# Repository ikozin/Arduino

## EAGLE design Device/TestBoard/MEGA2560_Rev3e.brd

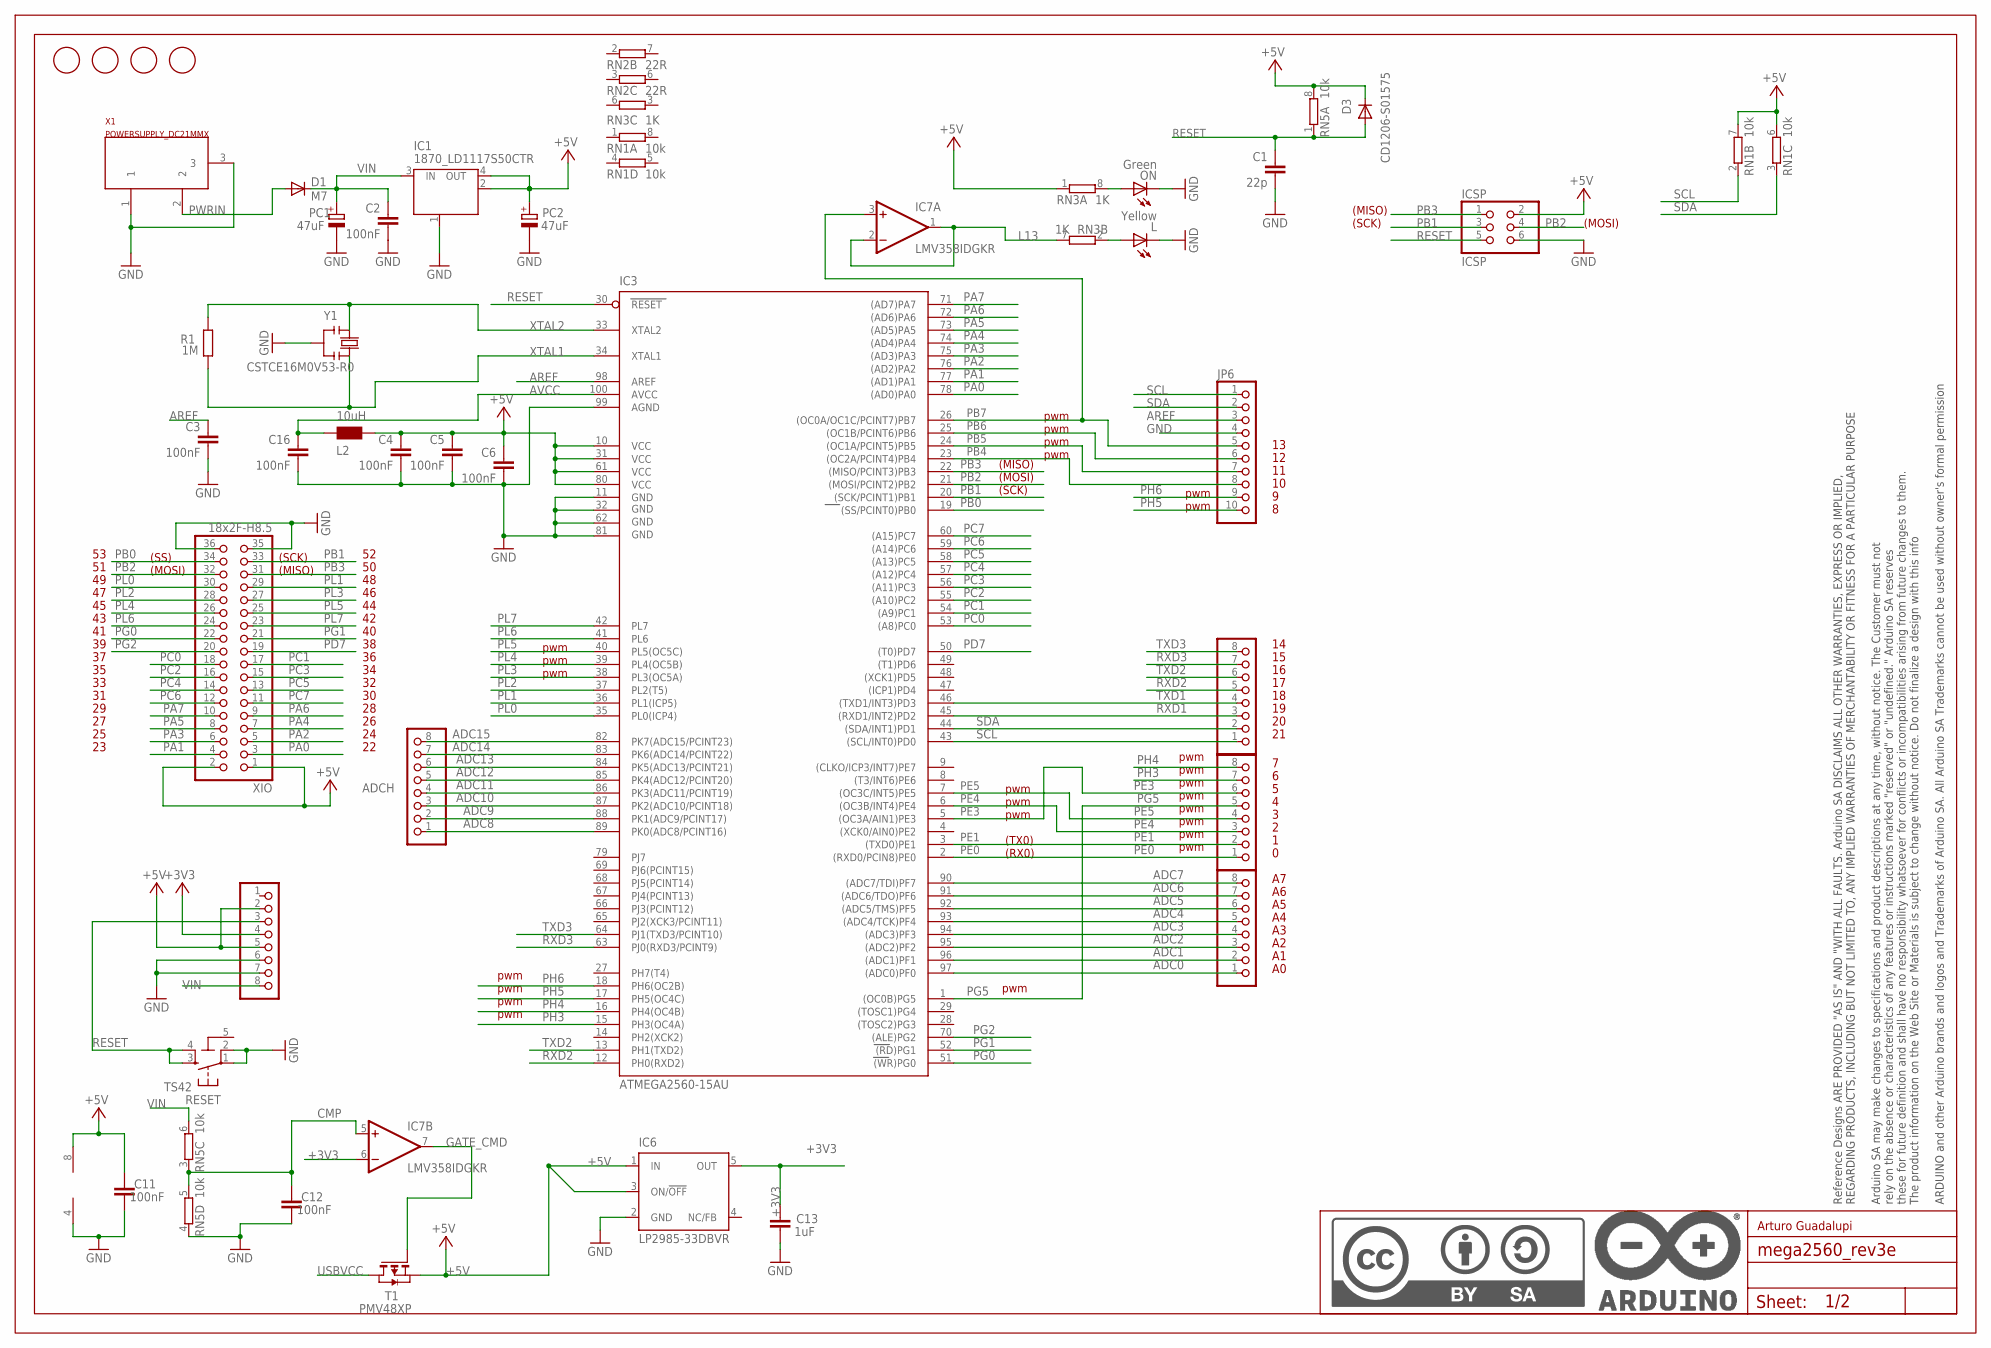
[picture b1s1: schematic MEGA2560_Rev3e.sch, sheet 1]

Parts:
ADCH: FH254-108DF08500V; 1X08
ADCL: FH254-108DF08500V; 1X08
C1: 22p; C0603-ROUND
C2, C3, C4, C5, C6, C11, C12, C16: 100nF; C0603-ROUND
C13: 1uF; C0603-ROUND
COMMUNICATION: FH254-108DF08500V; 1X08
D1: M7; SMB
D3: CD1206-S01575; MINIMELF
FD1, FD2, FD3, FD4: FIDUCIALMOUNT; FIDUCIA-MOUNT
IC1: 1870_LD1117S50CTR; LINEAR_SOT223
IC3: ATMEGA2560-15AU; TQFP100
IC6: LP2985-33DBVR; SOT23-DBV
IC7: LMV358IDGKR; MSOP08
ICSP: ICSP; 2X03
JP6: FH254-110DF08500V; 1X10
L: Yellow; CHIPLED_0805
L2: 10uH; 0805
ON: Green; CHIPLED_0805
PC1, PC2: 47uF; PANASONIC_D
POWER: FH254-108DF08500V; 1X08
PWML: FH254-108DF08500V; 1X08
R1: 1M; R0603-ROUND
RESET: TS42
RN1, RN5: 10k; CAY16
RN2: 22R; CAY16
RN3: 1K; CAY16
T1: PMV48XP; SOT-23; PART_NUMBER PMV48XP
U$1: DNP; FRAME
X1: POWERSUPPLY_DC21MMX; POWERSUPPLY_DC-21MM
XIO: 18x2F-H8.5; 2X18
Y1: CSTCE16M0V53-R0; RESONATOR

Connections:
5-GND: RESET.5 (5-GND)
+3V3: C13.2, IC6.5 (OUT), IC7.6 (-IN), POWER.4
+5V: C4.1, C5.1, C6.1, C11.2, D3.C, IC1.2 (OUT), IC1.4 (OUT), IC3.10 (VCC), IC3.31 (VCC1), IC3.61 (VCC2), IC3.80 (VCC3), IC6.1 (IN), IC6.3 (ON/!OFF), IC7.8 (V+), ICSP.2, L2.2, PC2.+, POWER.2, POWER.5, RN1.6 (2), RN1.7 (2), RN3.1, RN5.8 (2), T1.2 (S), XIO.1, XIO.2; also elsewhere on the board
ADC0: ADCL.1, IC3.97 ((ADC0)PF0)
ADC1: ADCL.2, IC3.96 ((ADC1)PF1)
ADC2: ADCL.3, IC3.95 ((ADC2)PF2)
ADC3: ADCL.4, IC3.94 ((ADC3)PF3)
ADC4: ADCL.5, IC3.93 ((ADC4/TCK)PF4)
ADC5: ADCL.6, IC3.92 ((ADC5/TMS)PF5)
ADC6: ADCL.7, IC3.91 ((ADC6/TDO)PF6)
ADC7: ADCL.8, IC3.90 ((ADC7/TDI)PF7)
ADC8: ADCH.1, IC3.89 (PK0(ADC8/PCINT16))
ADC9: ADCH.2, IC3.88 (PK1(ADC9/PCINT17))
ADC10: ADCH.3, IC3.87 (PK2(ADC10/PCINT18))
ADC11: ADCH.4, IC3.86 (PK3(ADC11/PCINT19))
ADC12: ADCH.5, IC3.85 (PK4(ADC12/PCINT20))
ADC13: ADCH.6, IC3.84 (PK5(ADC13/PCINT21))
ADC14: ADCH.7, IC3.83 (PK6(ADC14/PCINT22))
ADC15: ADCH.8, IC3.82 (PK7(ADC15/PCINT23))
AREF: C3.1, IC3.98 (AREF), JP6.3
AVCC: C16.1, IC3.100 (AVCC), L2.1
CMP: C12.2, IC7.5 (+IN), RN5.3 (1), RN5.5 (2)
GATE_CMD: IC7.7 (OUT), T1.3 (G)
GND: C1.2, C2.2, C3.2, C4.2, C5.2, C6.2, C11.1, C12.1, C13.1, C16.2, IC1.1 (GND/ADJ), IC3.11 (GND), IC3.32 (GND1), IC3.62 (GND2), IC3.81 (GND3), IC3.99 (AGND), IC6.2 (GND), IC7.4 (V-), ICSP.6, JP6.4, L.C, ON.C, PC1.-, PC2.-, POWER.6, POWER.7, RESET.1, RESET.2, RN5.4 (1), X1.1, X1.3, XIO.35, XIO.36, Y1.2; also elsewhere on the board
L13: IC7.1 (OUT), IC7.2 (-IN), RN3.7 (2)
unnamed: L.A, RN3.2 (1)
unnamed: ON.A, RN3.8 (2)
PA0: IC3.78 ((AD0)PA0), XIO.3
PA1: IC3.77 ((AD1)PA1), XIO.4
PA2: IC3.76 ((AD2)PA2), XIO.5
PA3: IC3.75 ((AD3)PA3), XIO.6
PA4: IC3.74 ((AD4)PA4), XIO.7
PA5: IC3.73 ((AD5)PA5), XIO.8
PA6: IC3.72 ((AD6)PA6), XIO.9
PA7: IC3.71 ((AD7)PA7), XIO.10
PB0: IC3.19 ((SS/PCINT0)PB0), XIO.34
PB1: IC3.20 ((SCK/PCINT1)PB1), ICSP.3, XIO.33
PB2: IC3.21 ((MOSI/PCINT2)PB2), ICSP.4, XIO.32
PB3: IC3.22 ((MISO/PCINT3)PB3), ICSP.1, XIO.31
PB4: IC3.23 ((OC2A/PCINT4)PB4), JP6.8
PB5: IC3.24 ((OC1A/PCINT5)PB5), JP6.7
PB6: IC3.25 ((OC1B/PCINT6)PB6), JP6.6
PB7: IC3.26 ((OC0A/OC1C/PCINT7)PB7), IC7.3 (+IN), JP6.5
PC0: IC3.53 ((A8)PC0), XIO.18
PC1: IC3.54 ((A9)PC1), XIO.17
PC2: IC3.55 ((A10)PC2), XIO.16
PC3: IC3.56 ((A11)PC3), XIO.15
PC4: IC3.57 ((A12)PC4), XIO.14
PC5: IC3.58 ((A13)PC5), XIO.13
PC6: IC3.59 ((A14)PC6), XIO.12
PC7: IC3.60 ((A15)PC7), XIO.11
PD7: IC3.50 ((T0)PD7), XIO.19
PE0: IC3.2 ((RXD0/PCIN8)PE0), PWML.1; also elsewhere on the board
PE1: IC3.3 ((TXD0)PE1), PWML.2; also elsewhere on the board
PE3: IC3.5 ((OC3A/AIN1)PE3), PWML.6
PE4: IC3.6 ((OC3B/INT4)PE4), PWML.3
PE5: IC3.7 ((OC3C/INT5)PE5), PWML.4
PG0: IC3.51 ((WR)PG0), XIO.22
PG1: IC3.52 ((RD)PG1), XIO.21
PG2: IC3.70 ((ALE)PG2), XIO.20
PG5: IC3.1 ((OC0B)PG5), PWML.5
PH3: IC3.15 (PH3(OC4A)), PWML.7
PH4: IC3.16 (PH4(OC4B)), PWML.8
PH5: IC3.17 (PH5(OC4C)), JP6.10
PH6: IC3.18 (PH6(OC2B)), JP6.9
PL0: IC3.35 (PL0(ICP4)), XIO.30
PL1: IC3.36 (PL1(ICP5)), XIO.29
PL2: IC3.37 (PL2(T5)), XIO.28
PL3: IC3.38 (PL3(OC5A)), XIO.27
PL4: IC3.39 (PL4(OC5B)), XIO.26
PL5: IC3.40 (PL5(OC5C)), XIO.25
PL6: IC3.41 (PL6), XIO.24
PL7: IC3.42 (PL7), XIO.23
PWRIN: D1.A, X1.2
RESET: C1.1, D3.A, IC3.30 (RESET), ICSP.5, POWER.3, RESET.3, RESET.4, RN5.1; also elsewhere on the board
RXD1: COMMUNICATION.3, IC3.45 ((RXD1/INT2)PD2)
RXD2: COMMUNICATION.5, IC3.12 (PH0(RXD2))
RXD3: COMMUNICATION.7, IC3.63 (PJ0(RXD3/PCINT9))
SCL: COMMUNICATION.1, IC3.43 ((SCL/INT0)PD0), JP6.1, RN1.2 (1)
SDA: COMMUNICATION.2, IC3.44 ((SDA/INT1)PD1), JP6.2, RN1.3 (1)
TXD1: COMMUNICATION.4, IC3.46 ((TXD1/INT3)PD3)
TXD2: COMMUNICATION.6, IC3.13 (PH1(TXD2))
TXD3: COMMUNICATION.8, IC3.64 (PJ1(TXD3/PCINT10))
USBVCC: T1.1 (D); also elsewhere on the board
VIN: C2.1, D1.C, IC1.3 (IN), PC1.+, POWER.8, RN5.6 (2)
XTAL1: IC3.34 (XTAL1), R1.1, Y1.3
XTAL2: IC3.33 (XTAL2), R1.2, Y1.1

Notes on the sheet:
(SCK)
(MISO)
(MOSI)
pwm
(TX0)
(RX0)
(SS)
Arturo Guadalupi

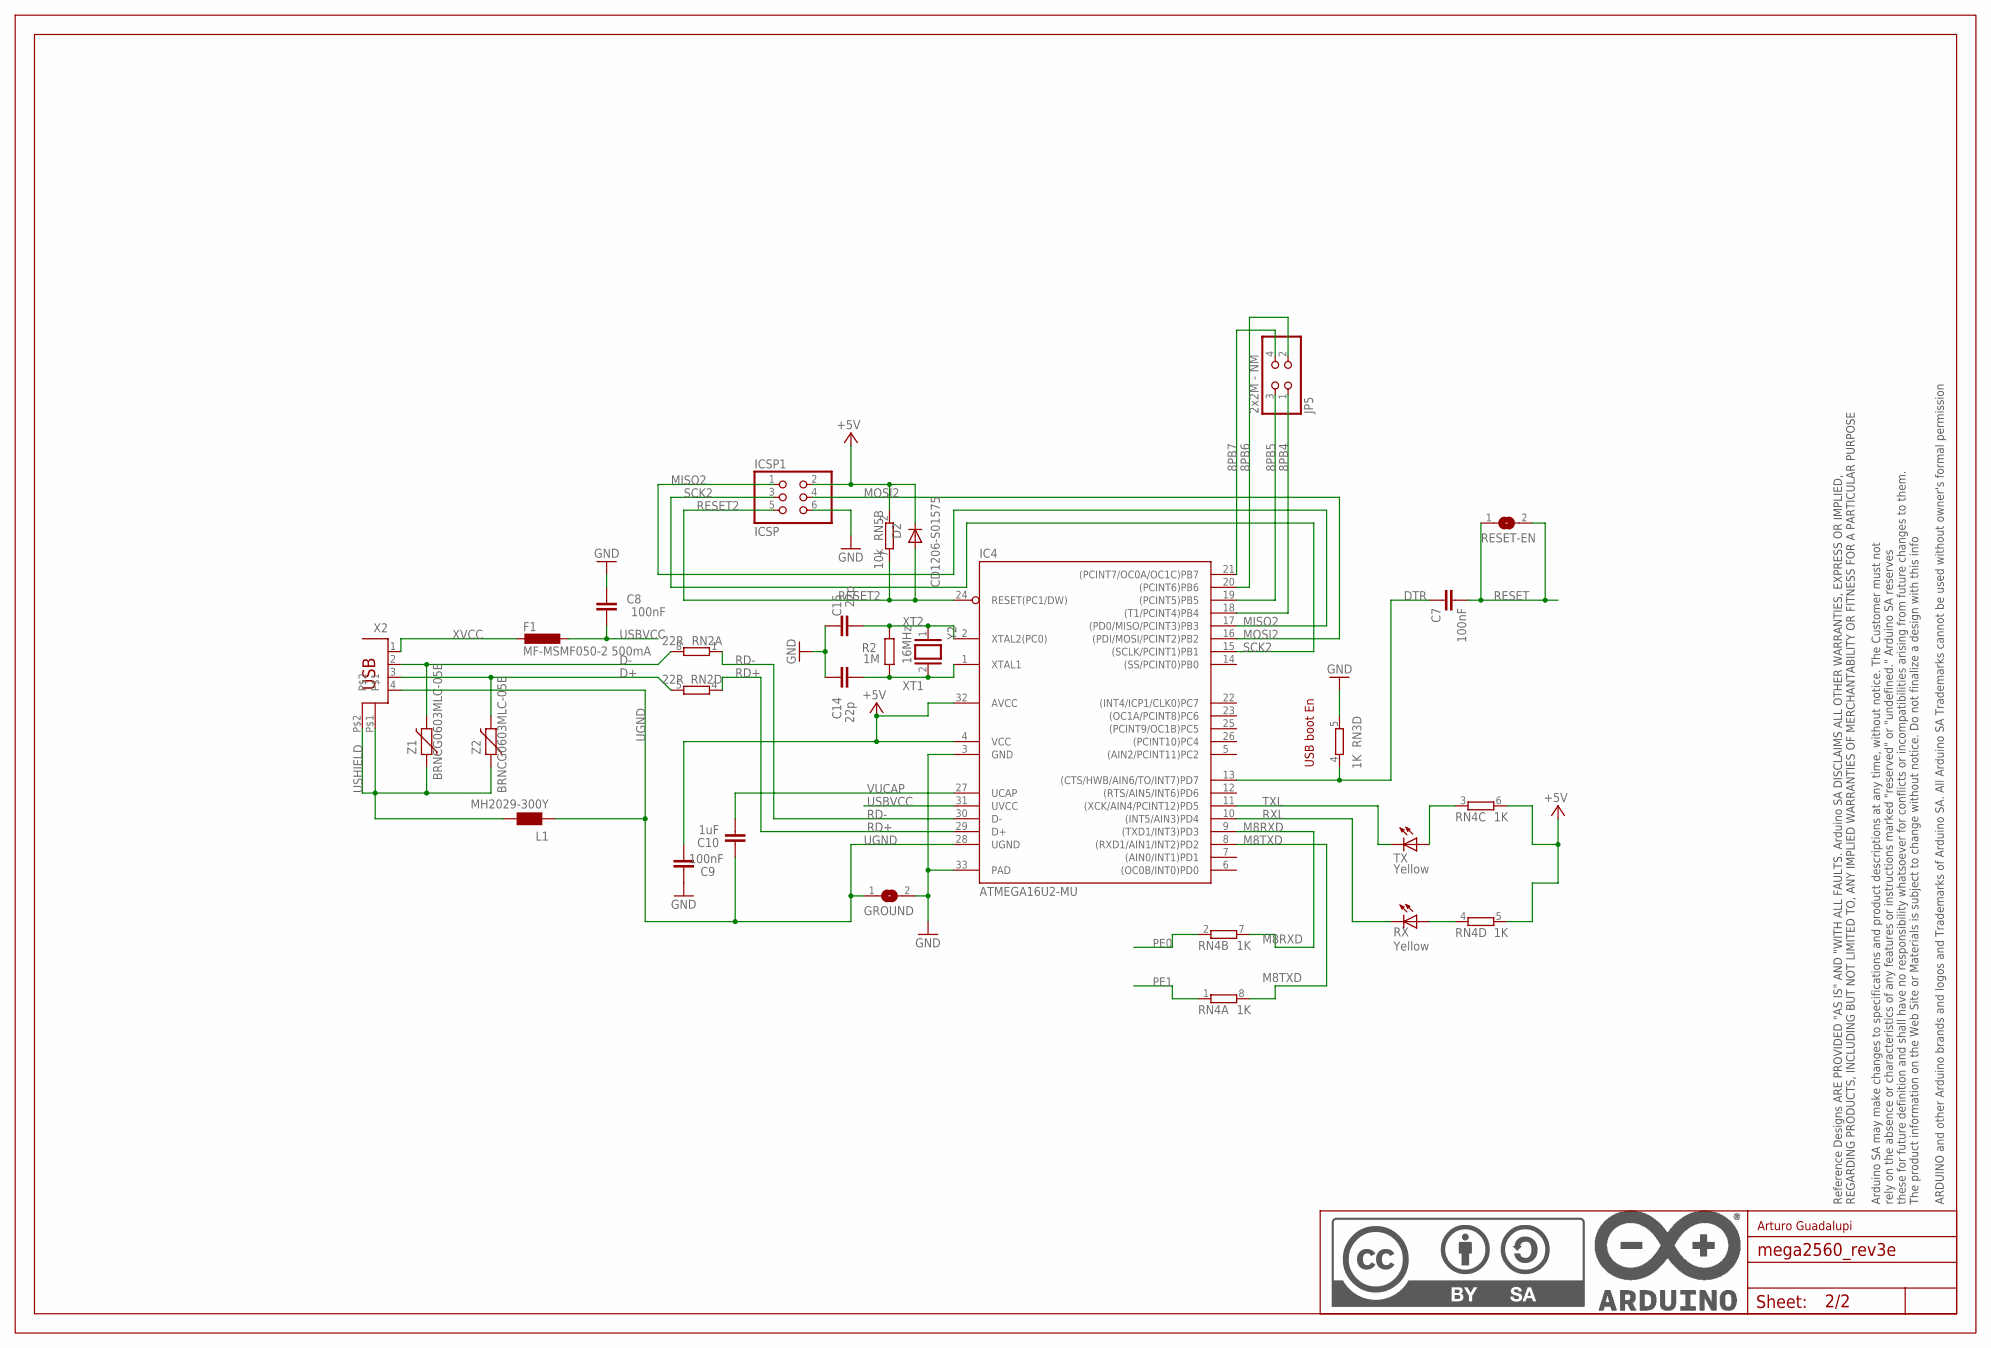
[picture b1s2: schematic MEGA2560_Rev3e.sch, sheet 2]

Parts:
C7, C8, C9: 100nF; C0603-ROUND
C10: 1uF; C0603-ROUND
C14, C15: 22p; C0603-ROUND
D2: CD1206-S01575; MINIMELF
F1: MF-MSMF050-2 500mA; L1812
GROUND: SJ
IC4: ATMEGA16U2-MU; MLF32
ICSP1: ICSP; 2X03
JP5: 2x2M - NM; 2X02
L1: MH2029-300Y; 0805
R2: 1M; R0603-ROUND
RESET-EN: SJ
RN2: 22R; CAY16
RN3, RN4: 1K; CAY16
RN5: 10k; CAY16
RX: Yellow; CHIPLED_0805
TX: Yellow; CHIPLED_0805
U$2: DNP; FRAME
X2: 0056_USB-B-S-RA-WT-SPCC; PN61729
Y2: 16MHz; QS
Z1, Z2: BRNCG0603MLC-05E; CT/CN0603

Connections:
8PB4: IC4.18 ((T1/PCINT4)PB4), JP5.1
8PB5: IC4.19 ((PCINT5)PB5), JP5.3
8PB6: IC4.20 ((PCINT6)PB6), JP5.2
8PB7: IC4.21 ((PCINT7/OC0A/OC1C)PB7), JP5.4
+5V: C9.1, D2.C, IC4.4 (VCC), IC4.32 (AVCC), ICSP1.2, RN4.5 (2), RN4.6 (2), RN5.2 (1); also elsewhere on the board
D+: RN2.5 (2), X2.3, Z2.2
D-: RN2.8 (2), X2.2, Z1.2
DTR: C7.1, IC4.13 ((CTS/HWB/AIN6/TO/INT7)PD7), RN3.4 (1)
GND: C8.2, C9.2, C14.2, C15.2, GROUND.2, IC4.3 (GND), IC4.33 (PAD), ICSP1.6, RN3.5 (2); also elsewhere on the board
M8RXD: IC4.9 ((TXD1/INT3)PD3), RN4.7 (2)
M8TXD: IC4.8 ((RXD1/AIN1/INT2)PD2), RN4.8 (2)
MISO2: IC4.17 ((PD0/MISO/PCINT3)PB3), ICSP1.1
MOSI2: IC4.16 ((PDI/MOSI/PCINT2)PB2), ICSP1.4
unnamed: RN4.4 (1), RX.A
unnamed: RN4.3 (1), TX.A
PE0: RN4.2 (1); also elsewhere on the board
PE1: RN4.1; also elsewhere on the board
RD+: IC4.29 (D+), RN2.4 (1)
RD-: IC4.30 (D-), RN2.1
RESET: C7.2, RESET-EN.1, RESET-EN.2; also elsewhere on the board
RESET2: D2.A, IC4.24 (RESET(PC1/DW)), ICSP1.5, RN5.7 (2)
RXL: IC4.10 ((INT5/AIN3)PD4), RX.C
SCK2: IC4.15 ((SCLK/PCINT1)PB1), ICSP1.3
TXL: IC4.11 ((XCK/AIN4/PCINT12)PD5), TX.C
UGND: C10.2, GROUND.1, IC4.28 (UGND), L1.1, X2.4
USBVCC: C8.1, F1.1, IC4.31 (UVCC); also elsewhere on the board
USHIELD: L1.2, X2.P$1, X2.P$2, Z1.1, Z2.1
VUCAP: C10.1, IC4.27 (UCAP)
XT1: C14.1, IC4.1 (XTAL1), R2.1, Y2.2
XT2: C15.1, IC4.2 (XTAL2(PC0)), R2.2, Y2.1
XVCC: F1.2, X2.1

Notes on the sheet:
USB boot En
Arturo Guadalupi

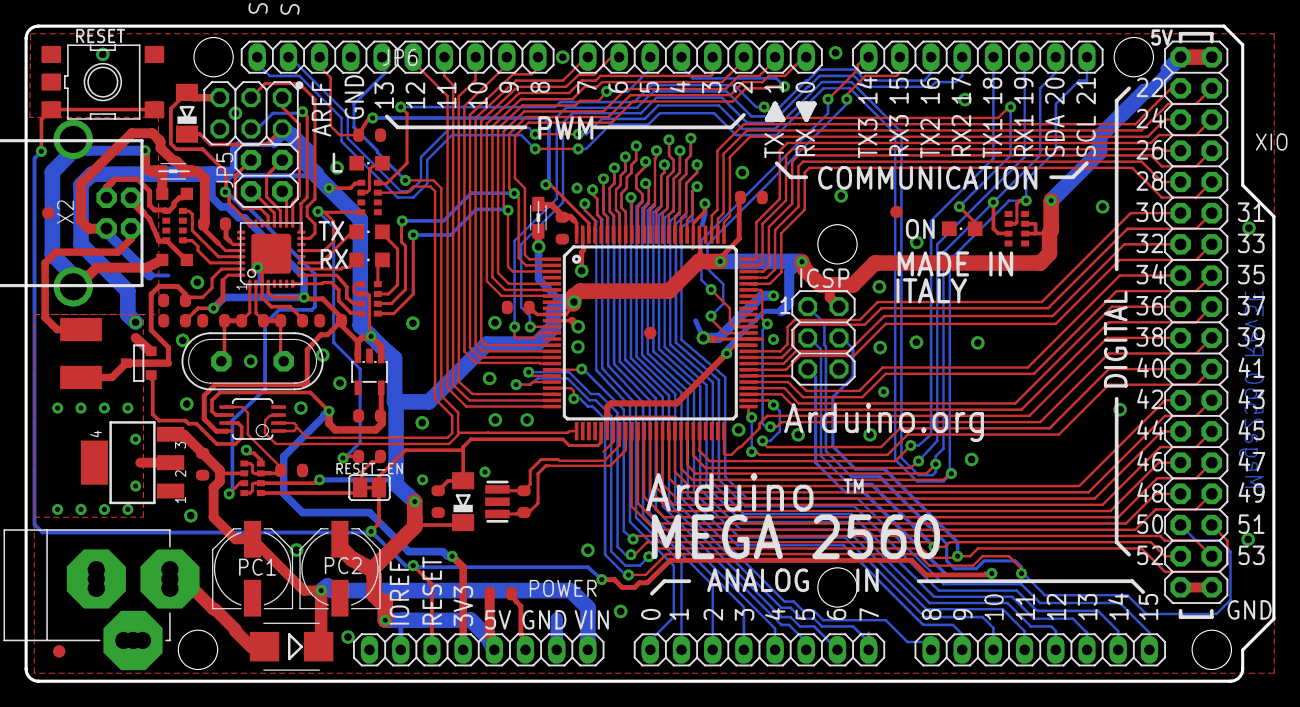
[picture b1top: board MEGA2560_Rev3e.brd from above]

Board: 2 copper layers, 101.6 x 53.3 mm, 66 parts (1 on the bottom side), 111 nets.

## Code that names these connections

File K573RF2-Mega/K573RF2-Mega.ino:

/*
К573РФ2
http://www.inp.nsk.su/~kozak/mem/mem18.htm
http://www.eandc.ru/pdf/mikroskhema/k573rf2.pdf
http://vip-cxema.org/index.php/home/mikrokontrollery/357-prostoj-kopirovshchik-rpzu-k573rf2-5

Распиновка платы К573РФ2

            CE OE
             |  |
        ------------------------
 A10 --|                        |
 A9  --|                        |
 A8  --|                        |
 A7  --|                        |
 A6  --|                        |-- GND
 A5  --|                        |-- VCC
 A4  --|                        |
 A3  --|                        |
 A2  --|                        |
 A1  --|                        |
 A0  --|                        |
        ------------------------
         |  |  |   |   |   |  |
        D0 D1 D2 D3 D4 D5 D6 D7

------------------------------------------------------------------------
Входы                      Выходы     Режим работы
------------------------------------------------------------------------
A0...A10  -CE  -OE  Vpp    D0...D7   
------------------------------------------------------------------------
  L/H      L    L    5v      Out      Считывание
  L/H      H    H   24v      L/H      Запись
   X       L    H    5v       Z       Невыбор
   X       H    X    5v       Z       Хранение(пониженная мощность)
   X       L    H   24v       Z       Запрет записи
  L/H      L    L   24v      Out      Проверка записи
------------------------------------------------------------------------

Распиновка К573РФ2
	  -------------
  1 -| A7      +5V |- 24
  2 -| A6       A8 |- 23
  3 -| A5       A9 |- 22
  4 -| A4      Vpp |- 21
  5 -| A3      ~OE |- 20
  6 -| A2      A10 |- 19
  7 -| A1      ~CE |- 18
  8 -| A0       D7 |- 17
  9 -| D0       D6 |- 16
 10 -| D1       D5 |- 15
 11 -| D2       D4 |- 14
 12 -| GND      D3 |- 13
	  -------------

 */

#ifndef __AVR_ATmega2560__
#error "Select board ATMEG2560"
#endif

#define ADDR0      (22)		//PA0
#define ADDR1      (23)		//PA1
#define ADDR2      (24)		//PA2
#define ADDR3      (25)		//PA3
#define ADDR4      (26)		//PA4
#define ADDR5      (27)		//PA5
#define ADDR6      (28)		//PA6
#define ADDR7      (29)		//PA7
#define ADDR8      (37)     //PC0
#define ADDR9      (36)     //PC1
#define ADDR10     (35)     //PC2
//#define ADDR11     (34)     //PC3
//#define ADDR12     (33)     //PC4
//#define ADDR13     (33)     //PC5
//#define ADDR14     (31)     //PC6
//#define ADDR15     (30)     //PC7

#define D0         (49)     //PL0
#define D1         (48)     //PL1
#define D2         (47)     //PL2
#define D3         (46)     //PL3
#define D4         (45)     //PL4
#define D5         (44)     //PL5
#define D6         (43)     //PL6
#define D7         (42)     //PL7

#define CE         (40)     //PG1
#define OE         (41)     //PG0


void setup ( )
{

  // Адрес,  контакты 22-30, порты A и C
  DDRA  = B11111111;
  DDRC  = B11111111;

  // Данные, контакты 42-49, порт L
  DDRL  = B00000000;

  // К573РФ2
  pinMode(CE, OUTPUT);
  pinMode(OE, OUTPUT);
  SetDisableMode();
  InitReadMode();

  Serial.begin(9600);
}

void loop ( )
{
}

//////////////////////////////////////////
// Хранение(пониженная мощность) К573РФ2
//////////////////////////////////////////
void SetDisableMode()
{
	digitalWrite(OE, LOW);
	digitalWrite(CE, HIGH);
}

//////////////////////////////////////////
// Считывание К573РФ2
//////////////////////////////////////////
void SetReadMode()
{
	digitalWrite(OE, LOW);
	digitalWrite(CE, LOW);
}

//////////////////////////////////////////
// Запись К573РФ2
//////////////////////////////////////////
void SetWriteMode()
{
	digitalWrite(OE, HIGH);
	digitalWrite(CE, HIGH);
}

//////////////////////////////////////////
// Данные на считывание
//////////////////////////////////////////
void InitReadMode()
{
	DDRL  = B00000000;
	PORTL = B11111111;
}

//////////////////////////////////////////
// Данные для записи
//////////////////////////////////////////
void InitWriteMode()
{
	DDRL  = B11111111;
}

//////////////////////////////////////////
// Читаем данные
//////////////////////////////////////////
uint8_t ReadData()
{
	return PORTL;
}

//////////////////////////////////////////
// Записваем данные
//////////////////////////////////////////
void WriteData(uint8_t data)
{
	PORTL = data;
}

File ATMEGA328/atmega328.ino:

//#define INSIDE_IRQ
#define LOG_CONSOLE
#include <MsTimer2.h>
#include <DHT.h>
#include "ledDisplay.h"
#include "DS3231.h"

/*
Adafruit Unified Sensor
DHT sensor library
MsTimer2
 
https://www.arduino.cc/en/Tutorial/ArduinoToBreadboard
http://codius.ru/articles/Arduino_UNO_4%D1%80%D0%B0%D0%B7%D1%80%D1%8F%D0%B4%D0%BD%D1%8B%D0%B9_7%D1%81%D0%B5%D0%B3%D0%BC%D0%B5%D0%BD%D1%82%D0%BD%D1%8B%D0%B9_%D0%B8%D0%B4%D0%B8%D0%BA%D0%B0%D1%82%D0%BE%D1%80_12_pin_3641BS_red
https://masterkit.ru/images/sets_scheme/nm7039box_sx.jpg
https://ecs7.tokopedia.net/img/product-1/2016/11/17/2550072/2550072_fa6ef4d0-76c7-4839-b123-9a678cd10d10.jpg

Плата: ATmega328 on a breadboard (8MHz internal clock)
       
Распиновка atmega328
	--------------------------------------------------
 1-|   | ~RST  | PC6 |             |  PC5 |  SCL | A5 |-28
 2-| 0 | RXD   | PD0 |             |  PC4 |  SDA | A4 |-27
 3-| 1 | TXD   | PD1 |             |  PC3 |      | A3 |-26
 4-| 2 |       | PD2 |             |  PC2 |      | A2 |-25
 5-| 3 |       | PD3 |             |  PC1 |      | A1 |-24
 6-| 4 |       | PD4 |             |  PC0 |      | A0 |-23
 7-|   | VCC   |     |             |  GND |      |    |-22
 8-|   | GND   |     |             | AREF |      |    |-21
 9-|   | XTAL1 | PB6 |             |  VCC |      |    |-20
10-|   | XTAL2 | PB7 |             |  PB5 |  SCK | 13 |-19
11-| 5 |       | PD5 |             |  PB4 | MISO | 12 |-18
12-| 6 |       | PD6 |             |  PB3 | MOSI | 11 |-17
13-| 7 |       | PD7 |             |  PB2 |   SS | 10 |-16
14-| 8 |       | PB0 |             |  PB1 |      |  9 |-15
	--------------------------------------------------

	   4-разрядный 7-сегментный индикатор с общим анодом
            1  A  F   2  3  B
 ___________|__|__|___|__|__|____________
|         |         |         |         |
|    A    |    A    |    A    |    A    |
| F     B | F     B | F     B | F     B |
|    G    |    G    |    G    |    G    |
| E     C | E     C | E     C | E     C |
|    D    |    D    |    D    |    D    |
|_______dp|_______dp|_______dp|_______dp|
            |  |  |   |  |  |
            E  D  dp  C  G  4


      ____________________________________________________________________________
     |                                                                            |
     |                          ___   ___   ___   ___                             |
     |                         |   | |   | |   | |   |                            |
     |                         |___| |___| |___| |___|                            |
     |                         |   | |   | |   | |   |                            |
     |                         |___|.|___|.|___|.|___|.                           |
     |                                                                            |
     |               ATmega328 on a breadboard (8MHz internal clock)              |
RST -|                                                                            |
RST -|                          RXD TXD                                           |
     |____________________________________________________________________________|
      |   |   |   |   |   |      |   |   |   |   |   |   |   |      |   |   |   |
     RST TXD RXD VCC     GND     0   1   2   3   4   5   6   7     SCL SDA VCC GND

     DTR TXO RXI VCC     GND                                 |     SCL SDA VCC GND
    __|___|___|___|___|___|__                                |    __|___|___|___|__
   |                         |                               |   |                 |
   |                         |                               |   |     DS3231      |
   |                         |                               |   |       RTC       |
   |                         |                               |   |     EEPROM      |
   |                         |                               |   |_________________|
   |_________________________|
            |       |                                        D  VCC GND
            |  USB  |                                      __|___|___|__
            |_______|                                     |             |
                                                          |   AM2301    |
                                                          |_____________|


*/

DHT dht(7, AM2301);
DS3231 ds3231;

long time = 0;
long temp = 0;
long hum = 0;

void setup()
{
  LED_DISPLAY::begin();
  dht.begin();
  ds3231.begin();
#ifdef LOG_CONSOLE
  Serial.begin(57600);
  Serial.println("Start");
#endif
  //ds3231.setDate(2, 4, 2022);  //day, month, year
  //ds3231.setTime(0, 34, 14);    //second, minute, hour
  //ds3231.setAgingOffset(-1);
}

byte cnt = 0;
void displayInfo()
{
  if (cnt & 0x08)
  {
    if (cnt & 0x04)
      LED_DISPLAY::setHumidity(hum);
    else
      LED_DISPLAY::setTemperature(temp);
  }
  else LED_DISPLAY::setTime(time);
}

void loop()
{
  time = ds3231.getTime();
  if (cnt & 0x04)
  {
    float h = dht.readHumidity();
    float t = dht.readTemperature();
    if (!isnan(h) && !isnan(t))
    {
      temp = lrint(t);
      hum = lrint(h);
    }
  }
#ifdef LOG_CONSOLE
  //Serial.println(time, HEX);
  Serial.print(ds3231.getTextDate());
  Serial.print(", ");
  Serial.print(ds3231.getTextTime());
  Serial.println();

  Serial.print(temp);
  Serial.println(" C");
  
   Serial.print(hum);
  Serial.println(" H");
#endif
  displayInfo();
  delay(500);
  cnt++;
}

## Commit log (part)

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2024-01-13 Архив
2024-01-22 diptrace
2024-01-25 stackDepth
2024-01-25 icons
2024-01-31 weather images
2024-02-02 fix ID4
2024-02-02 Переход на gio
2024-02-02 review
2024-02-02 remove
2024-02-02 ИД14
2024-02-02 #pragma once
2024-02-04 tool: binaries
2024-02-04 ИЕ19 + ИР37
2024-02-04 try_catch
2024-02-04 launch
2024-02-09 AT28C512
2024-02-09 ORION_ATX24
2024-02-17 K573RF2
2024-02-29 mt8816
2024-03-03 radio
2024-03-05 cleanup
2024-03-05 weather
2024-03-30 atx24
2024-03-30 testboard
2024-03-30 uiConverter
2024-07-03 mp1094
2024-07-14 rp2040
2024-07-20 esphome
2024-07-20 remote_receiver
2024-07-21 uodate
2024-07-22 refactoring
2024-07-28 refactor
2024-09-15 update radio
2024-10-03 mhzh19
2025-05-04 review+update

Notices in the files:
parts and their libraries:
Arduino-utility: Copyright (c) 2016-2017 Arduino LLC.  All right reserved.
